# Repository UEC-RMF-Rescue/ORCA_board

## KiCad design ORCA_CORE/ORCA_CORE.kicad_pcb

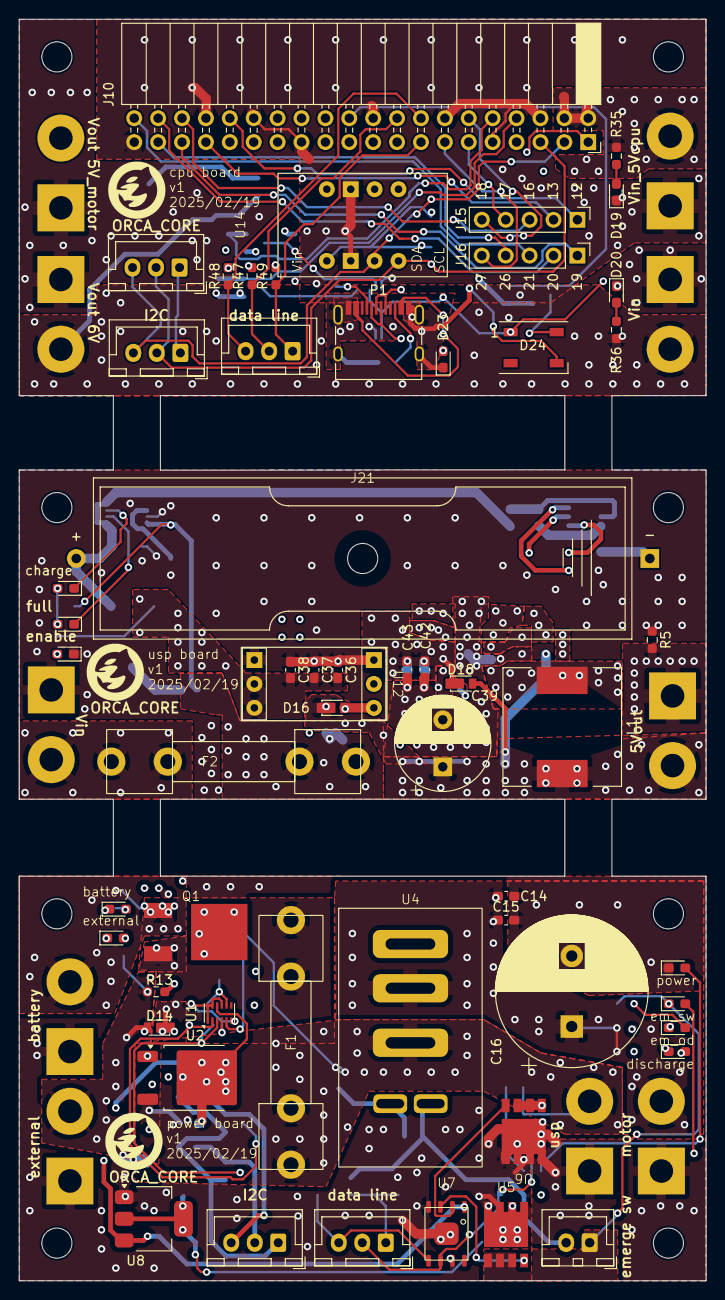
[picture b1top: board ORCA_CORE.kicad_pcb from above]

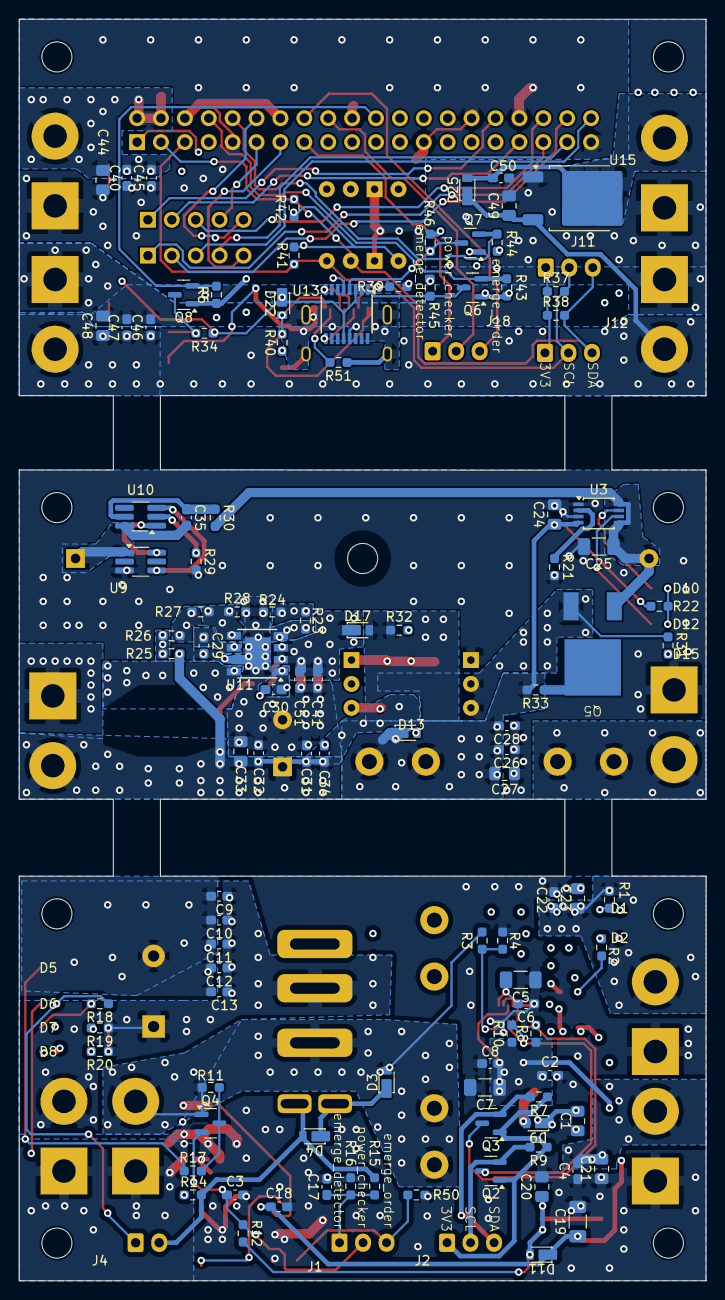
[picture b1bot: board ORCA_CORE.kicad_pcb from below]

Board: 4 copper layers, 73.0 x 134.1 mm, 184 parts (107 on the bottom side), 93 nets.

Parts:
C1, C49: 1u/50V; C_0805_2012Metric_Pad1.18x1.45mm_HandSolder
C2, C50: 0.1u25V; C_0603_1608Metric_Pad1.08x0.95mm_HandSolder
C3, C6, C8, C17, C30, C34, C35, C45: 0.1u; C_0603_1608Metric_Pad1.08x0.95mm_HandSolder
C4, C9, C10, C11, C12, C13, C14, C15, C18, C22, C26, C28, C31, C32, C36, C37, C38, C40, C41, C42, C43, C46, C47, C51: 4.7u; C_0603_1608Metric_Pad1.08x0.95mm_HandSolder
C5, C7, C25: 10u; C_1206_3216Metric_Pad1.33x1.80mm_HandSolder
C16: 4700u; CP_Radial_D16.0mm_P7.50mm
C19: 10u/50V; C_1206_3216Metric_Pad1.33x1.80mm_HandSolder
C20: 22u25V; C_0805_2012Metric_Pad1.18x1.45mm_HandSolder
C21, C23, C24, C27, C33, C44, C48: 1u; C_0805_2012Metric_Pad1.18x1.45mm_HandSolder
C29: 0.01u; C_0603_1608Metric_Pad1.08x0.95mm_HandSolder
C39: 1000u; CP_Radial_D10.0mm_P5.00mm
D1: LED_batt; LED_0603_1608Metric_Pad1.05x0.95mm_HandSolder
D2: LED_ex; LED_0603_1608Metric_Pad1.05x0.95mm_HandSolder
D3, D4, D9, D11, D13, D14, D16, D17, D18, D22, D25: CUHS20560; Diode_US2H
D5: LED_power; LED_0603_1608Metric_Pad1.05x0.95mm_HandSolder
D6: LED_emerge_switch; LED_0603_1608Metric_Pad1.05x0.95mm_HandSolder
D7: LED_emerge_order; LED_0603_1608Metric_Pad1.05x0.95mm_HandSolder
D8: LED_discharge; LED_0603_1608Metric_Pad1.05x0.95mm_HandSolder
D10: LED_charge; LED_0603_1608Metric_Pad1.05x0.95mm_HandSolder
D12: LED_full; LED_0603_1608Metric_Pad1.05x0.95mm_HandSolder
D15: LED_batt_enabled; LED_0603_1608Metric_Pad1.05x0.95mm_HandSolder
D19: LED_cpu; LED_0603_1608Metric_Pad1.05x0.95mm_HandSolder
D20: LED_motor; LED_0603_1608Metric_Pad1.05x0.95mm_HandSolder
D23: LED_usb; LED_0603_1608Metric_Pad1.05x0.95mm_HandSolder
D24: WS2812B; LED_WS2812B_PLCC4_5.0x5.0mm_P3.2mm
F1, F2: Fuse; fuse
H1, H2, H3, H4: Hole_power; MountingHole_3.2mm_M3
H5, H6: Hole_usp; MountingHole_3.2mm_M3
H9: Hole_cpu; MountingHole_3.2mm_M3
H10: Hole_cup; MountingHole_3.2mm_M3
J1, J18: data_line_power; JST_XH_B3B-XH-A_1x03_P2.50mm_Vertical
J2: I2C_power; JST_XH_B3B-XH-A_1x03_P2.50mm_Vertical
J3: Vout_motor; power_pad
J4: emergence; JST_XH_B2B-XH-A_1x02_P2.50mm_Vertical
J5: Vin_batt; power_pad
J6: Vin_ex; power_pad
J7: Vout_power2usp; power_pad
J8: Vin_power2usp; power_pad
J9: +5Vout_cpu; power_pad
J10: Raspberry_Pi_2_3; raspberrypi_Zero_W_Vertical
J11, J12: I2C; JST_XH_B3B-XH-A_1x03_P2.50mm_Vertical
J13: 6Vout; power_pad
J15, J16: Conn_01x05_Pin; PinHeader_1x05_P2.54mm_Vertical
J17: Vin_motor; power_pad
J19: +5Vin_cpu; power_pad
J20: 5Vout; power_pad
J21: Conn_01x02; BatteryHolder_1xAA_code
L1: 10u; L_12x12mm_H8mm_withmodel
ORCA_CORE: LOGO; ORCA_logo
ORCA_CORE#2, ORCA_CORE#3: LOGO; ORCA_logo
P1: USB_C_Receptacle_USB2.0; USB_C_Receptacle_XKB_U262-16XN-4BVC11
Q1, Q5: TJ60S04M3L; 2-7M1A
Q2, Q3, Q6, Q7, Q8: BSS138; SOT-23
Q4: IRLML6402; SOT-23
R1, R2, R14, R17, R18, R20, R22, R31, R35, R36, R40: 1k; R_0603_1608Metric_Pad0.98x0.95mm_HandSolder
R3, R4, R13, R15, R16, R26: 4.7k; R_0603_1608Metric_Pad0.98x0.95mm_HandSolder
R5: 0; R_0603_1608Metric_Pad0.98x0.95mm_HandSolder
R6, R7, R8, R9, R10, R11, R12, R34, R37, R38, R41, R42, R43, R44, R45, R46, R47, R48, R49, R50: 2.2k; R_0603_1608Metric_Pad0.98x0.95mm_HandSolder
R19: 360; R_0603_1608Metric_Pad0.98x0.95mm_HandSolder
R21: 1.2k; R_0603_1608Metric_Pad0.98x0.95mm_HandSolder
R23, R24: 100k; R_0603_1608Metric_Pad0.98x0.95mm_HandSolder
R25: 47k; R_0603_1608Metric_Pad0.98x0.95mm_HandSolder
R27: 510; R_0603_1608Metric_Pad0.98x0.95mm_HandSolder
R28, R32, R33: 10k; R_0603_1608Metric_Pad0.98x0.95mm_HandSolder
R29: 2k; R_0603_1608Metric_Pad0.98x0.95mm_HandSolder
R30: 100; R_0603_1608Metric_Pad0.98x0.95mm_HandSolder
R39, R51: 5.1k; R_0603_1608Metric_Pad0.98x0.95mm_HandSolder
U1: LTC2301IMS; TDFN-12_2x3mm_P0.5mm
U2, U15: NJM78055DL1; TO-252-2
U3: CN3058E; TSSOP-8_3x3mm_P0.65mm
U4: RH1B-UDC6V; RH1-U
U5, U6: TPH11006NL; 2-5Q1S
U7: NJW4860; TSOP8-M1
U8: AZ1117-3.3; SOT-223-3_TabPin2
U9: FS8205; TSOT-23-6_HandSoldering
U10: HY2112; TSOT-23-6_HandSoldering
U11: AP64502; Diodes_SO-8EP
U12: TPS61230A__board; TPS61230A
U13: FT230XS; SSOP-16_3.9x4.9mm_P0.635mm
U14: BNO055

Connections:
+3V3_cpu: J10.1 (3V3), J10.17 (3V3), J11.1, J12.1, Q6.1 (G), Q7.1 (G), Q8.1 (G), R6.1, R37.1, R38.1, R41.1, R42.1, R43.1, R44.1, U14.1 (VDD)
+3V3_power: C20.1, D11.2 (A), R12.2, U8.2 (Vout)
+5V_cpu: C40.1, C44.1, C45.1, D22.1 (K), D24.1 (VDD), J10.2 (5V), J10.4 (5V), J19.2, R34.1, R35.1, R45.1, R46.1, U13.3 (VCCIO), U13.12 (VCC)
+5V_cpu2servo: C50.1, D25.2 (A), J20.2, U15.2 (Vout)
+5V_power: C2.1, C7.1, C8.1, C18.1, C19.1, D9.2 (A), D11.1 (K), R8.1, R10.1, U1.10 (VDD), U2.2 (Vout), U7.1 (Vdd), U8.3 (Vin)
+6V_cpu: C46.1, C47.1, C48.1, C49.1, D25.1 (K), J13.2, J17.2, R36.1, U15.3 (Vin)
+6V_power: C1.1, D3.2 (A), D9.1 (K), F1.2, J7.2, Q4.1 (G), R3.1, R11.2, U2.3 (Vin), U4.9
+BATT_power: C22.2, C23.2, J5.2, Q1.1 (D), R1.2
+VDD_power: C4.2, C21.2, D14.2 (A), J6.2, R2.1, R13.2
+VDD_usp: C24.1, C26.2, C27.2, C28.2, D13.1 (K), D17.2 (A), F2.1, R22.1, R32.1, R33.2, U3.4 (VIN)
/cpu/GPIO12: J10.32 (PWM0/GPIO12), J15.1
/cpu/GPIO13: J10.33 (PWM1/GPIO13), J15.2
/cpu/GPIO16: J10.36 (GPIO16), J15.3
/cpu/GPIO17: J10.11 (GPIO17), J15.4
/cpu/GPIO18: J10.12 (GPIO18/PWM0), J15.5
/cpu/GPIO19: J10.35 (GPIO19/MISO1), J16.1
/cpu/GPIO20: J10.38 (GPIO20/MOSI1), J16.2
/cpu/GPIO21: J10.40 (GPIO21/SCLK1), J16.3
/cpu/GPIO26: J10.37 (GPIO26), J16.4
/cpu/GPIO27: J10.13 (GPIO27), J16.5
/cpu/emerg_detector: J10.15 (GPIO22), J18.1, R49.1
/cpu/emerge_order: J10.16 (GPIO23), J18.3, R48.1
/cpu/power_checker: J10.18 (GPIO24), J18.2, R47.1
/power/SCL_3V3: J2.2, Q2.2 (S), R9.2
/power/SDA_3V3: J2.3, Q3.2 (S), R7.2
/power/Vout_motor: C9.1, C10.1, C11.1, C12.1, C13.1, C14.1, C15.1, C16.1, J3.2, R19.1, R20.1, U4.5
/power/emerg_detector: C17.1, J1.1, R15.2, R16.1
/power/emerge_order: J1.3, R50.2, U7.5 (INB)
/power/power_checker: C3.1, J1.2, Q4.2 (S), R12.1, U7.6 (INA)
/usp/Vin: F2.2, J8.2
GND: C1.2, C2.2, C3.2, C4.1, C5.1, C6.1, C7.2, C8.2, C9.2, C10.2, C11.2, C12.2, C13.2, C14.2, C15.2, C16.2, C17.2, C18.2, C19.2, C20.2, C21.1, C22.1, C23.1, C24.2, C25.2, C26.1, C27.1, C28.1, C29.2, C31.1, C32.1, C33.1, C34.1, C36.1, C37.1, C38.1, C39.2, C41.1, C42.1, C43.1, C46.2, C47.2, C48.2, C49.2, C50.2, C51.1, D1.1 (K), D2.1 (K), D5.1 (K), D7.1 (K), D13.2 (A), D15.1 (K), D20.1 (K), J3.1, J5.1, J6.1, J7.1, J8.1, J13.1, J17.1, J20.1, R4.2, R5.1, R16.2, R21.2, R24.2, R28.2, R29.2, R32.2, R50.1, U1.1 (GND), U1.4 (GND), U1.6 (IN-), U1.9 (GDN), U1.11 (AD1), U1.12 (AD0), U2.1 (GND), U3.1 (TEMP), U3.3 (GND), U5.5, U5.6, U5.7, U5.8, U6.5, U6.6, U6.7, U6.8, U7.4 (GND), U7.7 (GND), U8.1 (GND), U9.3, U11.7 (GND), U11.9 (PAD), U12.3 (GND), U15.1 (GND)
GND1: J9.1, R5.2
GND2: C40.2, C44.2, C45.2, D19.1 (K), D23.1 (K), D24.3 (VSS), J10.6 (GND), J10.9 (GND), J10.14 (GND), J10.20 (GND), J10.25 (GND), J10.30 (GND), J10.34 (GND), J10.39 (GND), J19.1, P1.A1 (GND), P1.A12 (GND), P1.B1 (GND), P1.B12 (GND), P1.S1 (SHIELD), R39.1, R47.2, R48.2, R49.2, R51.1, U13.5 (GND), U13.13 (GND), U14.2 (GND), U14.7 (GND)
unnamed: D1.2 (A), R1.1
unnamed: D2.2 (A), R2.2
unnamed: D3.1 (K), D4.1 (K), U4.14
unnamed: D4.2 (A), J4.2, R14.1, R15.1, U4.13
unnamed: D5.2 (A), R17.1
unnamed: D6.2 (A), R14.2
unnamed: D6.1 (K), J4.1, R18.1, U5.1, U5.2, U5.3
unnamed: D7.2 (A), R18.2
unnamed: D8.2 (A), R20.2
unnamed: D8.1 (K), R19.2, U6.1, U6.2, U6.3
unnamed: D10.2 (A), D12.2 (A), R22.2
unnamed: D10.1 (K), U3.7 (CHRG)
unnamed: D12.1 (K), U3.6 (DONE)
unnamed: D14.1 (K), F1.1, Q1.3 (S)
unnamed: D15.2 (A), R31.2
unnamed: D19.2 (A), R35.2
unnamed: D20.2 (A), R36.2
unnamed: D22.2 (A), P1.A4 (VBUS), P1.A9 (VBUS), P1.B4 (VBUS), P1.B9 (VBUS), R40.1
unnamed: D23.2 (A), R40.2
unnamed: P1.A5 (CC1), R39.2
unnamed: P1.B5 (CC2), R51.2
unnamed: Q1.2 (G), R13.1
unnamed: Q4.3 (D), R11.1, R17.2
unnamed: Q5.2 (G), R33.1
unnamed: R23.2, R24.1
unnamed: R25.1, R26.1
unnamed: R26.2, R27.1
unnamed: R3.2, R4.1, U1.5 (IN+)
unnamed: C5.2, C6.2, U1.8 (REFCOMP)
unnamed: R21.1, U3.2 (ISET)
unnamed: U6.4, U7.2 (OUTA)
unnamed: U5.4, U7.3 (OUTB)
unnamed: R29.1, U10.2 (CS)
unnamed: U9.4, U10.3 (OC)
unnamed: U9.6, U10.1 (OD)
unnamed: C35.1, R30.1, U10.5 (VDD)
unnamed: C30.2, U11.1 (BST)
unnamed: R27.2, R28.1, U11.5 (FB)
unnamed: R23.1, U11.4 (RT/CLK)
unnamed: C29.1, U11.6 (SS)
unnamed: C30.1, L1.1, U11.8 (SW)
unnamed: P1.A7 (D-), P1.B7 (D-), U13.9 (USBDM)
unnamed: P1.A6 (D+), P1.B6 (D+), U13.8 (USBDP)
RXD_3V3: J10.10 (GPIO15/RXD), Q7.2 (S), R44.2
RXD_5V: Q7.3 (D), R46.2, U13.4 (RXD)
SCL: J10.5 (SCL/GPIO3), J11.2, J12.2, R37.2, R41.2, U14.4 (SCL)
SCL_5V: Q2.3 (D), R10.2, U1.3 (SCL)
SDA: J10.3 (SDA/GPIO2), J11.3, J12.3, R38.2, R42.2, U14.3 (SDA)
SDA_5V: Q3.3 (D), R8.2, U1.2 (SDA)
TXD_3V3: J10.8 (GPIO14/TXD), Q6.2 (S), R43.2
TXD_5V: Q6.3 (D), R45.2, U13.1 (TXD)
VBUS_power: J2.1, Q2.1 (G), Q3.1 (G), R7.1, R9.1
batt+: C25.1, J21.2, Q5.1 (D), R30.2, U3.5 (BAT), U3.8 (FB)
batt-: C35.2, J21.1, U9.1, U10.6 (VSS)
full_color_led_3V3: J10.22 (GPIO25), Q8.2 (S), R6.2
full_color_led_5V: D24.4 (DIN), Q8.3 (D), R34.2
reg_down: C41.2, C42.2, C43.2, C51.2, D17.1 (K), D18.1 (K), U11.2 (Vin), U11.3 (EN)
reg_down_out: C31.2, C32.2, C33.2, C34.2, C39.1, D16.1 (K), D18.2 (A), J9.2, L1.2, R25.2
reg_up: C36.2, C37.2, C38.2, Q5.3 (S), R31.1, U12.1 (VIN), U12.2 (EN)
reg_up_out: D16.2 (A), U12.4 (VOUT)

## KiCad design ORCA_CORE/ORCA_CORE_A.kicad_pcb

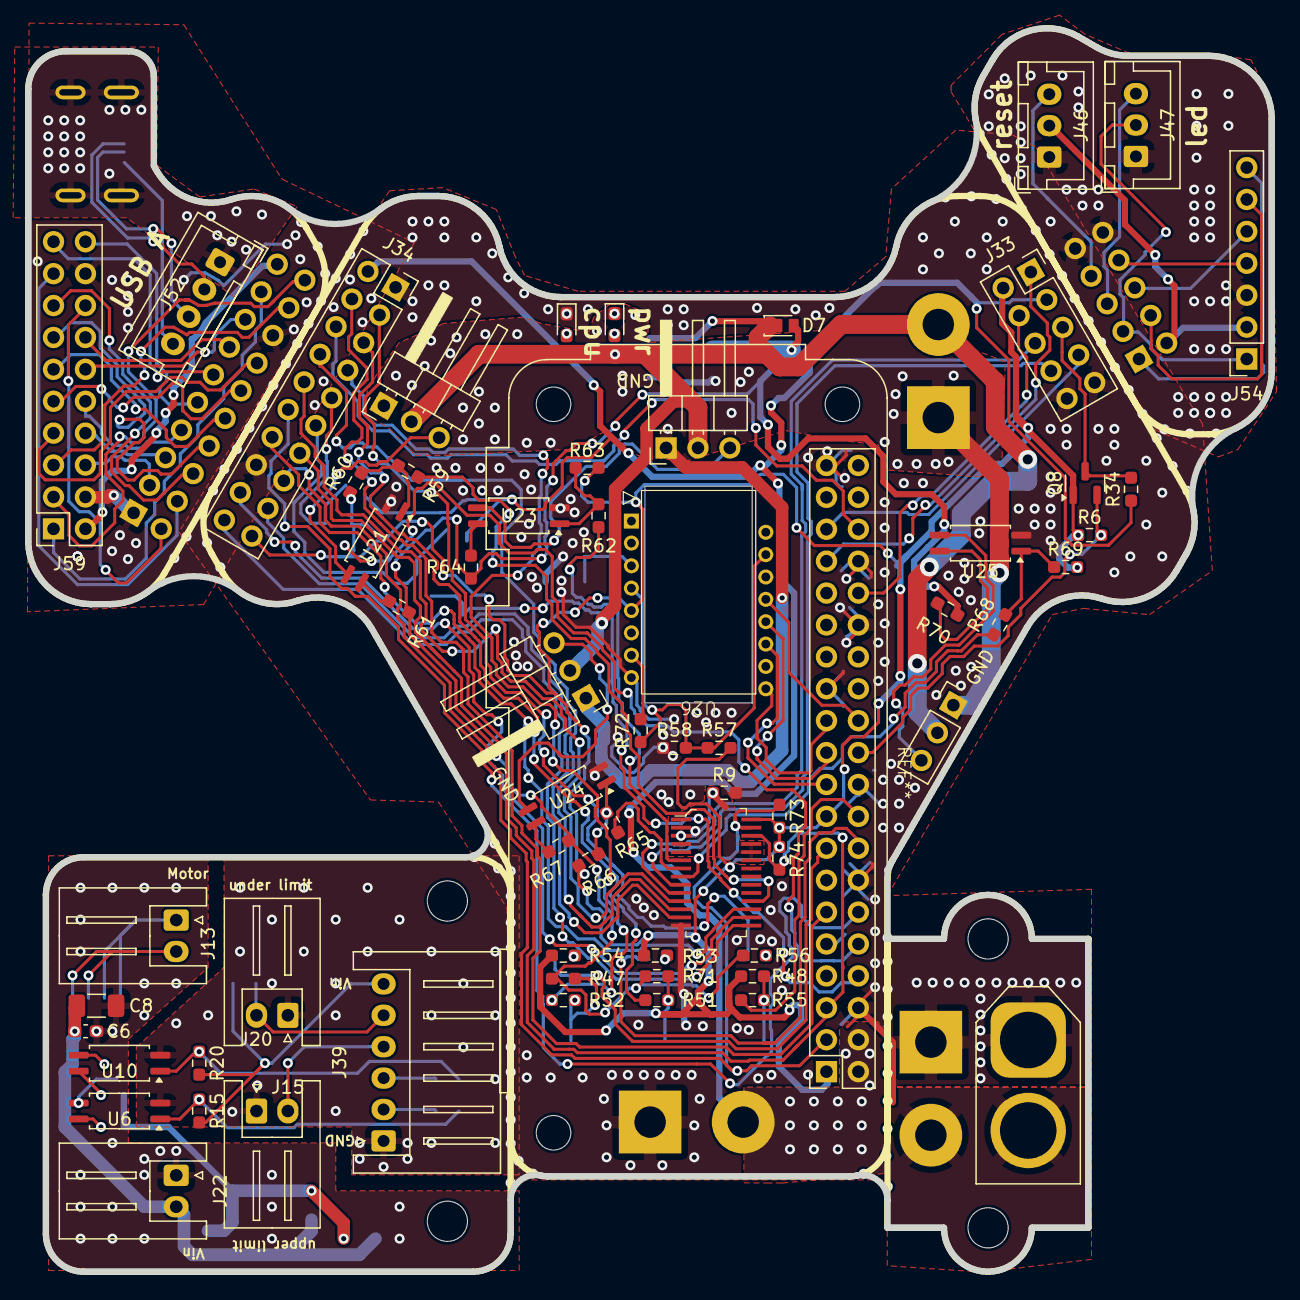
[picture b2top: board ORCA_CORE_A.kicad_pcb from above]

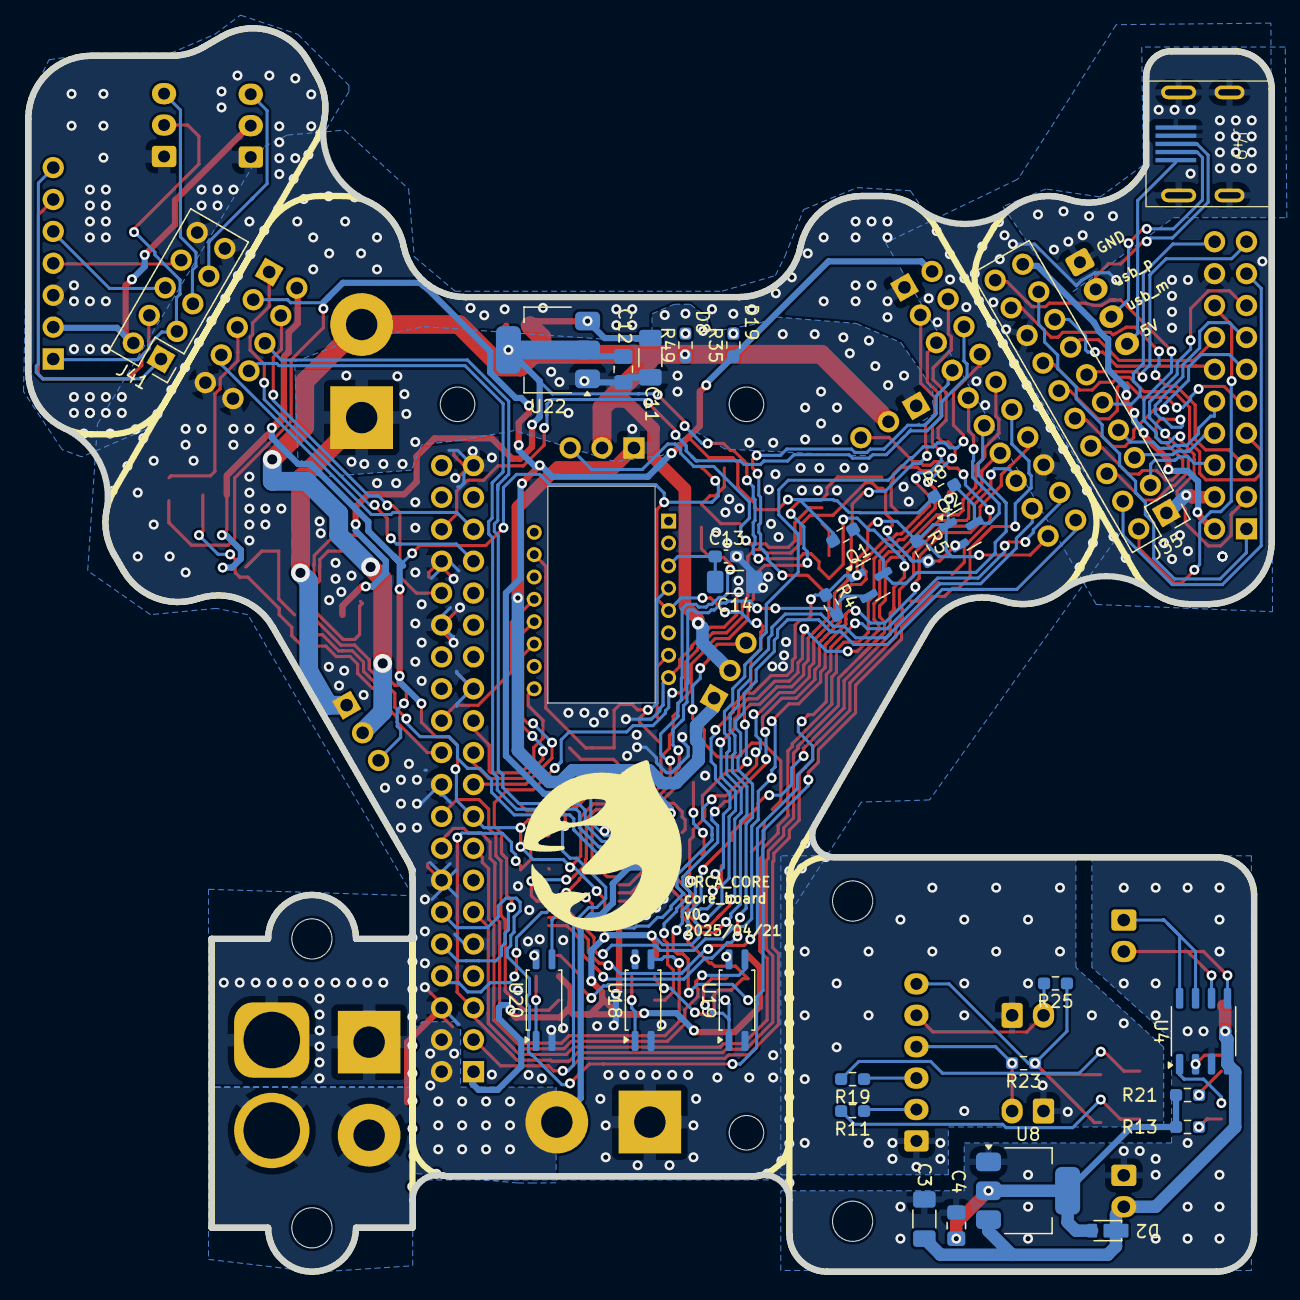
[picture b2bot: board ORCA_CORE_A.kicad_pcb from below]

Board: 2 copper layers, 99.0 x 99.0 mm, 100 parts (30 on the bottom side), 108 nets.

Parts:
C3, C11: 10u/50V; C_1206_3216Metric_Pad1.33x1.80mm_HandSolder
C4, C12: 22u25V; C_0805_2012Metric_Pad1.18x1.45mm_HandSolder
C6, C13: 0.1u; C_0603_1608Metric_Pad1.08x0.95mm_HandSolder
C8: 220u; C_1206_3216Metric_Pad1.33x1.80mm_HandSolder
C14: 10u; C_1206_3216Metric_Pad1.33x1.80mm_HandSolder
D2, D7: CUHS20560; Diode_US2H
D8: pwr_motor; LED_0603_1608Metric_Pad1.05x0.95mm_HandSolder
D19: pwr_cpu; LED_0603_1608Metric_Pad1.05x0.95mm_HandSolder
H7, H8: Hole_Vext; MountingHole_3.2mm_M3
H15, H16: Hole_md; MountingHole_3.2mm_M3
J1: Vext_in; AMASS_XT60_Vertifcal_withmodel_female
J6: Vext_out; power_pad
J8: wheel_front; PinHeader_1x03_P2.54mm_Horizontal
J9: wheel_right; PinHeader_1x03_P2.54mm_Horizontal
J10: Raspberry_Pi_2_3; raspberrypi_Zerp_W_horisontal
J11: wheel_left; PinHeader_1x03_P2.54mm_Vertical
J13: md_out; JST_XH_S2B-XH-A_1x02_P2.50mm_Horizontal
J15: limit_sw_upper; JST_XH_S2B-XH-A_1x02_P2.50mm_Horizontal
J18: +6V_motor; power_pad
J19: +5Vin_cpu; power_pad
J20: limit_sw_under; JST_XH_S2B-XH-A_1x02_P2.50mm_Horizontal
J22: Vin_motor; JST_XH_S2B-XH-A_1x02_P2.50mm_Horizontal
J33: cpu_female_left; PinSocket_2x05_P2.54mm_Vertical
J34: cpu_female_right; PinSocket_2x10_P2.54mm_Vertical
J35: hat_male_right; PinHeader_2x10_P2.54mm_Vertical
J39: md_arm; JST_XH_S6B-XH-A_1x06_P2.50mm_Horizontal
J41: cpu_male_left; PinHeader_2x05_P2.54mm_Vertical
J44: servo_camera; PinHeader_1x03_P2.54mm_Horizontal
J46: reset; JST_XH_B3B-XH-A_1x03_P2.50mm_Vertical
J47: led; JST_XH_B3B-XH-A_1x03_P2.50mm_Vertical
J49: USB_B_Micro; ZX60-B-5S(31)
J52: usb_A; JST_XH_B4B-XH-A_1x04_P2.50mm_Vertical
J54: base_left; PinSocket_1x07_P2.54mm_Vertical
J59: base_right; PinSocket_2x10_P2.54mm_Vertical
Q1, Q2, Q8: BSS138; SOT-23
R4, R5, R6, R7, R8, R13, R15, R20, R21, R23, R25, R34, R47, R48, R53, R54, R56, R60, R61, R63, R64, R66, R67, R69, R70, R71, R73, R74: 2.2k; R_0603_1608Metric_Pad0.98x0.95mm_HandSolder
R9, R72: 10k; R_0603_1608Metric_Pad0.98x0.95mm_HandSolder
R11, R19, R51, R52, R55, R59, R62, R65, R68: 100; R_0603_1608Metric_Pad0.98x0.95mm_HandSolder
R35, R49: 1k; R_0603_1608Metric_Pad0.98x0.95mm_HandSolder
R57: 1.2k; R_0603_1608Metric_Pad0.98x0.95mm_HandSolder
R58: 2k; R_0603_1608Metric_Pad0.98x0.95mm_HandSolder
U2: PCA9685PW_Q900_118; TSSOP-28_W4.40mm
U4: AM2837; SOP-8_3.9x4.9mm_P1.27mm
U6, U10, U18, U19, U20, U21, U23, U24, U25: TLP293; SOIC-4_4.55x2.6mm_P1.27mm
U8, U22: AZ1117-3.3; SOT-223-3_TabPin2
U26: PMW3360

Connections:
+3V3: C4.1, D2.2 (A), J10.1 (3V3), J10.17 (3V3), J33.2, J34.19, Q1.1 (G), Q2.1 (G), Q8.1 (G), R4.1, R5.1, R6.1, R13.2, R21.2, R48.2, R53.2, R54.2, R57.2, R60.2, R63.2, R66.2, R69.2, R73.2, R74.2, U2.28 (VDD), U8.2 (Vout), U26.5 (VDDIO)
+3V3_motor: C12.1, D7.2 (A), R47.2, R56.2, R61.2, R64.2, R67.2, R70.2, R71.2, U22.2 (Vout)
+5V: J10.2 (5V), J10.4 (5V), J19.2, J33.3, J34.2, R7.1, R8.1, R34.1, R35.1
+6V: C3.1, C6.1, C8.1, C11.1, D2.1 (K), D7.1 (K), J8.2, J9.2, J11.2, J18.2, J22.2, J44.2, R49.1, U4.4 (VCC), U8.3 (Vin), U22.3 (Vin)
/cpu/GPIO12: J10.32 (PWM0/GPIO12), J33.4
/cpu/GPIO13: J10.33 (PWM1/GPIO13), J33.1
/cpu/GPIO16: J10.36 (GPIO16), J34.6
/cpu/GPIO17: J10.11 (GPIO17), J34.4
/cpu/GPIO18: J10.12 (GPIO18/PWM0), J34.12
/cpu/LED0: R62.1, U2.6 (LED0)
/cpu/LED1: R65.1, U2.7 (LED1)
/cpu/LED2: R68.1, U2.8 (LED2)
/cpu/LED3: J33.8, U2.9 (LED3)
/cpu/LED4: J33.6, U2.10 (LED4)
/cpu/LED5: J34.10, U2.11 (LED5)
/cpu/LED6: J34.8, U2.12 (LED6)
/cpu/LED7: J34.17, U2.13 (LED7)
/cpu/LED8: J34.20, U2.15 (LED8)
/cpu/LED9: J34.18, U2.16 (LED9)
/cpu/LED10: J34.14, U2.17 (LED10)
/cpu/LED11: R59.1, U2.18 (LED11)
/cpu/RXD_5V: J34.9, Q2.3 (D), R8.2
/cpu/TXD_5V: J34.11, Q1.3 (D), R7.2
/cpu/emerge_detector: J34.7, R52.1
/cpu/emerge_order: J34.3, U20.3
/cpu/led: J33.5, Q8.3 (D), R34.2
/cpu/power_checker: J34.5, R51.1
/cpu/rest: J10.35 (GPIO19/MISO1), J33.7
/cpu_hat/+5V_usb: J49.1 (VBUS), J52.4
/cpu_hat/GND_usb: J49.4 (ID), J49.5 (GND), J49.SH (Shield), J52.1
/cpu_hat/IN_A_arm: J35.10, J59.11
/cpu_hat/IN_A_fork: J41.8, J54.4
/cpu_hat/IN_B_arm: J35.8, J59.13
/cpu_hat/IN_B_fork: J41.6, J54.5
/cpu_hat/RX: J35.9, J59.20
/cpu_hat/SCL: J35.13, J59.14
/cpu_hat/SDA: J35.15, J59.12
/cpu_hat/TX: J35.11, J59.19
/cpu_hat/emerge_detector: J35.7, J59.10
/cpu_hat/emerge_order: J35.3, J59.6
/cpu_hat/enable_arm: J35.12, J59.9
/cpu_hat/led: J41.5, J47.3
/cpu_hat/limit_sw_under_arm: J35.4, J59.17
/cpu_hat/limit_sw_under_fork: J41.1, J54.7
/cpu_hat/limit_sw_upper_arm: J35.6, J59.15
/cpu_hat/limit_sw_upper_fork: J41.4, J54.6
/cpu_hat/power_checker: J35.5, J59.8
/cpu_hat/reset: J41.7, J46.3
/cpu_hat/servo_0: J35.17, J59.1
/cpu_hat/servo_1: J35.20, J59.3
/cpu_hat/servo_2: J35.18, J59.5
/cpu_hat/servo_3: J35.14, J59.7
/cpu_hat/usb_m: J49.2 (D-), J52.3
/cpu_hat/usb_p: J49.3 (D+), J52.2
/md_arm/IN_A: J39.2, R11.1
/md_arm/IN_B: J39.3, R19.1
/md_arm/limit_sw_under: J20.2, J39.5, R25.2
/md_arm/limit_sw_upper: J15.2, J39.4, R23.2
CS0: J10.24 (~CE0/GPIO8), U26.13 (NCS)
GND: C3.2, C4.2, C6.2, C8.2, C11.2, C12.2, D8.1 (K), J8.1, J9.1, J11.1, J18.1, J22.1, J44.1, U4.3 (GND), U8.1 (GND), U22.1 (GND)
GND1: C13.1, C14.1, D19.1 (K), J1.1, J6.1, J10.6 (GND), J10.9 (GND), J10.14 (GND), J10.20 (GND), J10.25 (GND), J10.30 (GND), J10.34 (GND), J10.39 (GND), J15.1, J19.1, J20.1, J33.9, J33.10, J34.1, J34.16, J35.1, J35.16, J39.1, J41.9, J41.10, J46.1, J47.1, J54.3, J59.4, J59.18, R9.2, R58.1, U2.14 (VSS), U6.2, U10.2, U18.2, U19.2, U20.2, U21.2, U23.2, U24.2, U25.2, U26.8 (GND)
MISO: J10.21 (MISO0/GPIO9), U26.12 (MISO)
MOSI: J10.19 (MOSI0/GPIO10), U26.11 (MOSI)
unnamed: D8.2 (A), R49.2
unnamed: D19.2 (A), R35.2
unnamed: J1.2, J6.2
unnamed: J8.3, U23.3
unnamed: J9.3, U24.3
unnamed: J11.3, U25.3
unnamed: J13.1, U4.7 (OUT_A2), U4.8 (OUT_A1)
unnamed: J13.2, U4.5 (OUT_B2), U4.6 (OUT_B1)
unnamed: J44.3, U21.3
unnamed: R11.2, R15.1, U6.1
unnamed: R13.1, U6.4
unnamed: R19.2, R20.1, U10.1
unnamed: R21.1, U10.4
unnamed: R47.1, R52.2, U19.1
unnamed: R48.1, R55.2, U20.1
unnamed: R51.2, R71.1, U18.1
unnamed: R53.1, U18.4
unnamed: R54.1, U19.4
unnamed: R56.1, U20.4
unnamed: R59.2, R60.1, U21.1
unnamed: R61.1, U21.4
unnamed: R62.2, R63.1, U23.1
unnamed: R64.1, U23.4
unnamed: R65.2, R66.1, U24.1
unnamed: R67.1, U24.4
unnamed: R68.2, R69.1, U25.1
unnamed: R70.1, U25.4
unnamed: R9.1, U2.1 (A0), U2.2 (A1), U2.3 (A2), U2.4 (A3), U2.5 (A4), U2.23 (~OE), U2.24 (A5), U2.25 (EXTCLK)
unnamed: U4.1 (IN_A), U6.3
unnamed: U4.2 (IN_B), U10.3
unnamed: R57.1, R58.2, R72.1, U26.4 (VDD), U26.15 (LED_P)
unnamed: R72.2, U26.7 (NRESET)
unnamed: C13.2, C14.2, U26.3 (VDDPIX)
RXD_3V3: J10.10 (GPIO15/RXD), Q2.2 (S), R5.2
SCL: J10.5 (SCL/GPIO3), J34.13, R74.1, U2.26 (SCL)
SCLK: J10.23 (SCLK0/GPIO11), U26.9 (SCLK)
SDA: J10.3 (SDA/GPIO2), J34.15, R73.1, U2.27 (SDA)
TXD_3V3: J10.8 (GPIO14/TXD), Q1.2 (S), R4.2
Vin_3V3_cpu_hat: J35.19, J41.2, J46.2, J54.2, J59.2
Vin_cpu_hat: J35.2, J41.3, J47.2, J54.1, J59.16
Vin_md: J39.6, R15.2, R20.2, R23.1, R25.1
emerge_detector_out: J10.15 (GPIO22), U19.3
emerge_order_in: J10.18 (GPIO24), R55.1
full_color_led_3V3: J10.22 (GPIO25), Q8.2 (S), R6.2
power_checker_out: J10.16 (GPIO23), U18.3

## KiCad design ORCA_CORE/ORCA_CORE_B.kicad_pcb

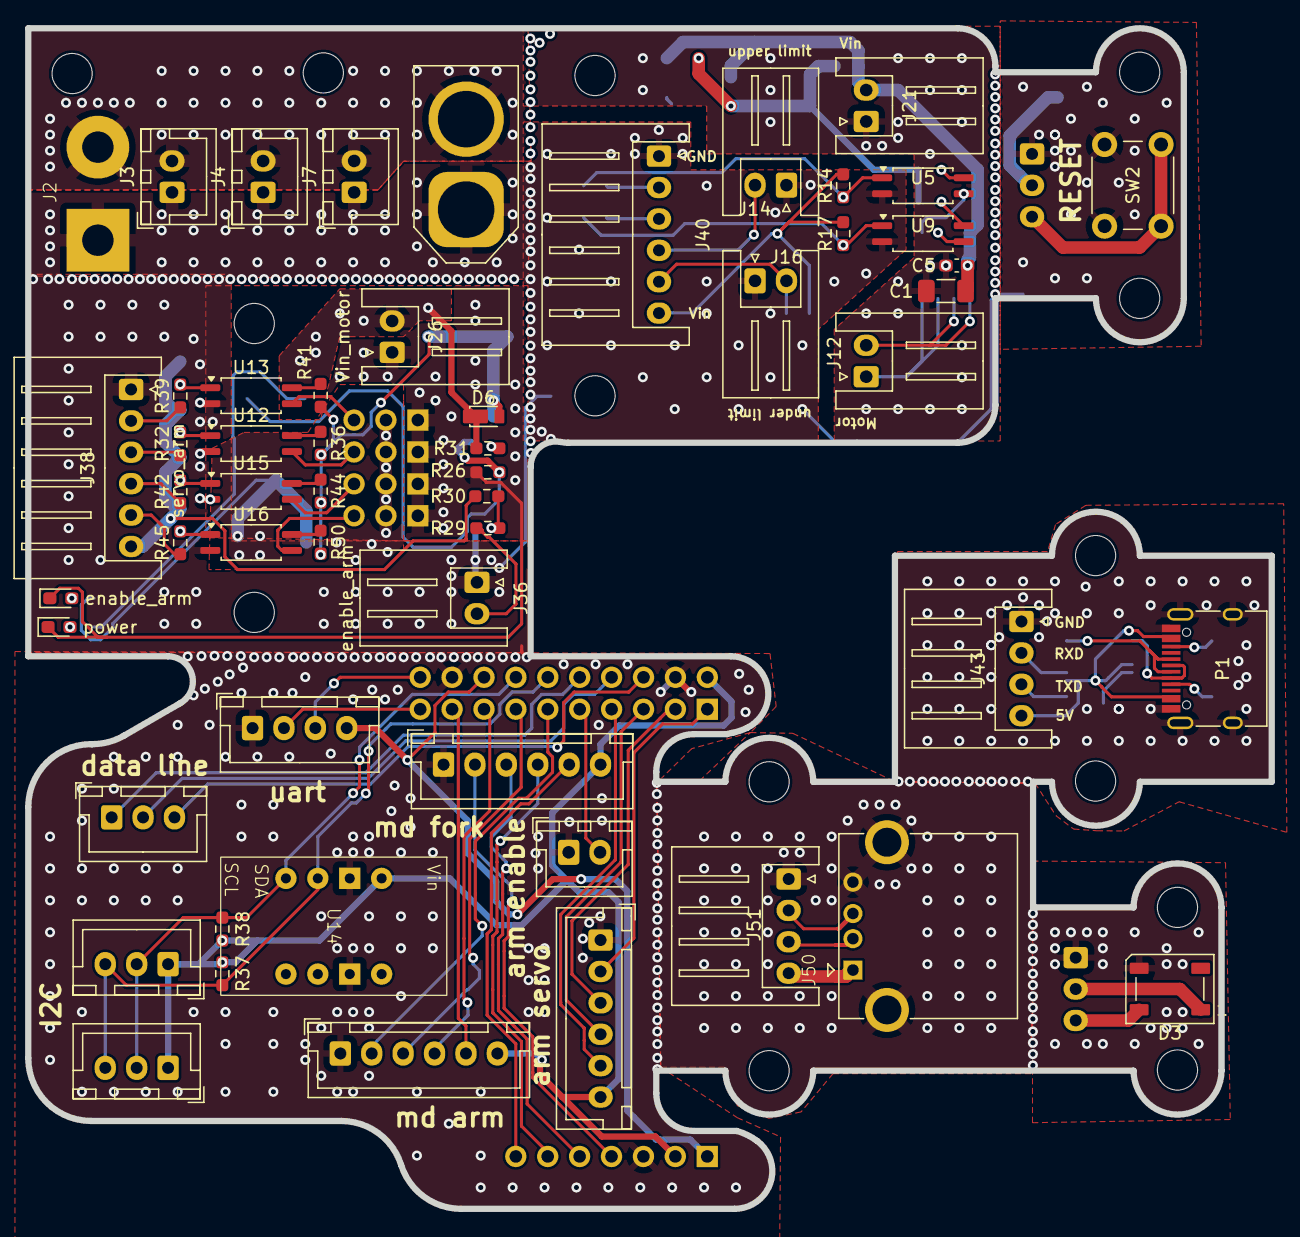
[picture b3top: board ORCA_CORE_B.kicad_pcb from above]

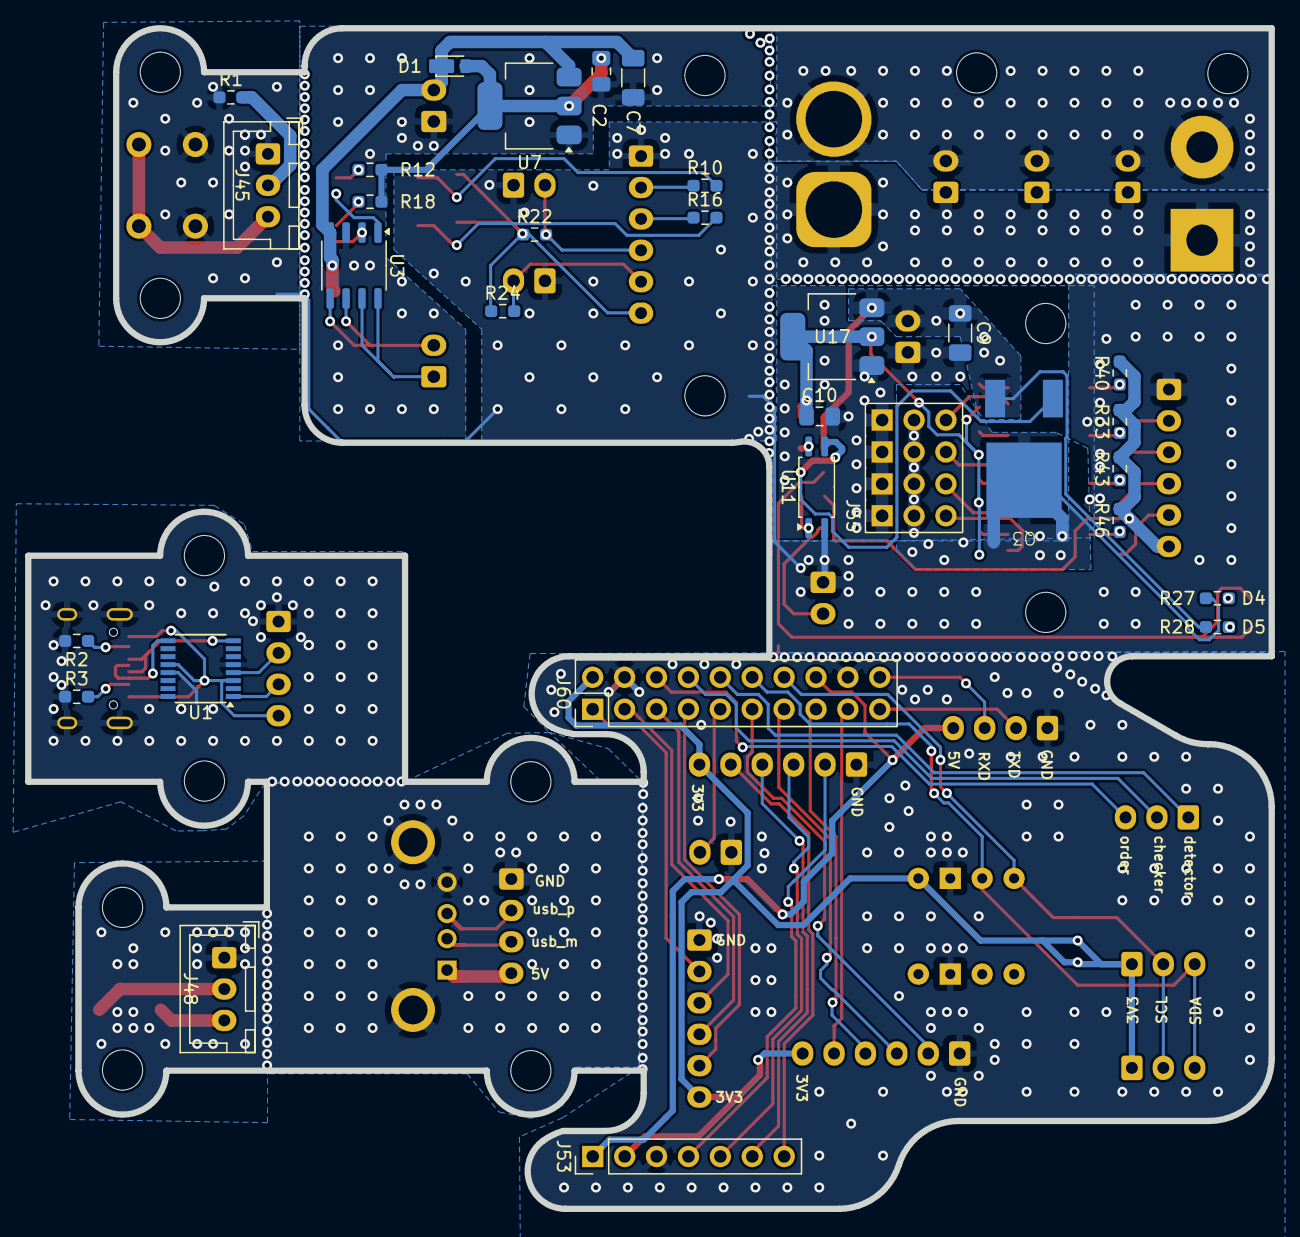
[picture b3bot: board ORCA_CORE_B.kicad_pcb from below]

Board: 2 copper layers, 99.0 x 94.0 mm, 100 parts (31 on the bottom side), 79 nets.

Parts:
C1, C9: 10u/50V; C_1206_3216Metric_Pad1.33x1.80mm_HandSolder
C2, C10: 22u25V; C_0805_2012Metric_Pad1.18x1.45mm_HandSolder
C5: 0.1u; C_0603_1608Metric_Pad1.08x0.95mm_HandSolder
C7: 220u; C_1206_3216Metric_Pad1.33x1.80mm_HandSolder
D1, D6: CUHS20560; Diode_US2H
D3: WS2812B; LED_WS2812B_PLCC4_5.0x5.0mm_P3.2mm
D4: enable_arm; LED_0603_1608Metric_Pad1.05x0.95mm_HandSolder
D5: power; LED_0603_1608Metric_Pad1.05x0.95mm_HandSolder
H1, H2: Hole_uart; MountingHole_3.2mm_M3
H3, H4: Hole_led; MountingHole_3.2mm_M3
H5, H6: Hole_reset; MountingHole_3.2mm_M3
H11, H12: Hole_Vhub; MountingHole_3.2mm_M3
H13, H14: Hole_md; MountingHole_3.2mm_M3
H23, H24: Hole_usbA; MountingHole_3.2mm_M3
H25, H26: Hole_arm; MountingHole_3.2mm_M3
J2: 6Vout; power_pad
J3, J4, J7: 6Vout; JST_XH_B2B-XH-A_1x02_P2.50mm_Vertical
J5: 6Vin; AMASS_XT60_Vertifcal_withmodel_female
J12: md_out; JST_XH_S2B-XH-A_1x02_P2.50mm_Horizontal
J14: limit_sw_upper; JST_XH_S2B-XH-A_1x02_P2.50mm_Horizontal
J16: limit_sw_under; JST_XH_S2B-XH-A_1x02_P2.50mm_Horizontal
J17: data_line_power; JST_XH_B3B-XH-A_1x03_P2.50mm_Vertical
J21, J26: Vin_motor; JST_XH_S2B-XH-A_1x02_P2.50mm_Horizontal
J23: md_arm; JST_XH_B6B-XH-A_1x06_P2.50mm_Vertical
J24: md_fork; JST_XH_B6B-XH-A_1x06_P2.50mm_Vertical
J25: servo_arm; JST_XH_B6B-XH-A_1x06_P2.50mm_Vertical
J31: I2C_1; JST_XH_B3B-XH-A_1x03_P2.50mm_Vertical
J32: I2C_2; JST_XH_B3B-XH-A_1x03_P2.50mm_Vertical
J36: enable_arm; JST_XH_S2B-XH-A_1x02_P2.50mm_Horizontal
J37: enable_arm; JST_XH_B2B-XH-A_1x02_P2.50mm_Vertical
J38: servo_arm; JST_XH_S6B-XH-A_1x06_P2.50mm_Horizontal
J40: md_fork; JST_XH_S6B-XH-A_1x06_P2.50mm_Horizontal
J42: uart; JST_XH_B4B-XH-A_1x04_P2.50mm_Vertical
J43: uart_device; JST_XH_S4B-XH-A_1x04_P2.50mm_Horizontal
J45: reset; JST_XH_B3B-XH-A_1x03_P2.50mm_Vertical
J48: led; JST_XH_B3B-XH-A_1x03_P2.50mm_Vertical
J50: USB_A; TypeA_connector_KUSBX-AS1N-B
J51: usb_A_device; JST_XH_S4B-XH-A_1x04_P2.50mm_Horizontal
J53: cover_left; PinHeader_1x07_P2.54mm_Vertical
J55: servo connectors; PinHeader_03x04_P2.54mm_Vertical
J60: cover_right; PinHeader_2x10_P2.54mm_Vertical
P1: USB_C_Receptacle_USB2.0; USB_C_Receptacle_XKB_U262-16XN-4BVC11
Q3: TJ60S04M3L; 2-7M1A
R1: 560; R_0603_1608Metric_Pad0.98x0.95mm_HandSolder
R2, R3: 5.1k; R_0603_1608Metric_Pad0.98x0.95mm_HandSolder
R10, R16, R29, R32, R39, R42, R45: 100; R_0603_1608Metric_Pad0.98x0.95mm_HandSolder
R12, R14, R17, R18, R22, R24, R30, R33, R36, R37, R38, R40, R41, R43, R44, R46, R50: 2.2k; R_0603_1608Metric_Pad0.98x0.95mm_HandSolder
R26: 10k; R_0603_1608Metric_Pad0.98x0.95mm_HandSolder
R27, R28: 1k; R_0603_1608Metric_Pad0.98x0.95mm_HandSolder
R31: 47; R_0603_1608Metric_Pad0.98x0.95mm_HandSolder
SW2: REST_sw; SW_PUSH_6mm
U1: FT230XS; SSOP-16_3.9x4.9mm_P0.635mm
U3: AM2837; SOP-8_3.9x4.9mm_P1.27mm
U5, U9, U11, U12, U13, U15, U16: TLP293; SOIC-4_4.55x2.6mm_P1.27mm
U7, U17: AZ1117-3.3; SOT-223-3_TabPin2
U14: BNO055

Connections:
+3V3: C2.1, C10.1, D1.2 (A), D6.2 (A), R12.2, R18.2, R36.2, R41.2, R44.2, R50.2, U7.2 (Vout), U17.2 (Vout)
+6V: C1.1, C5.1, C7.1, D1.1 (K), J21.2, U3.4 (VCC), U7.3 (Vin)
+6V_in: C9.1, D6.1 (K), J26.2, Q3.3 (S), R28.2, R31.2, U17.3 (Vin)
+6V_out: J55.2, J55.5, J55.8, J55.11, Q3.1 (D), R27.1
/arm/enable_arm: J36.2, R29.1
/arm/servo_0: J38.2, R39.1
/arm/servo_1: J38.3, R32.1
/arm/servo_2: J38.4, R42.1
/arm/servo_3: J38.5, R45.1
/cpu_hat/IN_A_arm_out: J23.2, J60.11
/cpu_hat/IN_A_fork_out: J24.2, J53.4
/cpu_hat/IN_B_arm_out: J23.3, J60.13
/cpu_hat/IN_B_fork_out: J24.3, J53.5
/cpu_hat/RX_out: J42.3, J60.20
/cpu_hat/TX_out: J42.2, J60.19
/cpu_hat/enable_arm_out: J37.2, J60.9
/cpu_hat/limit_sw_under_arm_in: J23.5, J60.17
/cpu_hat/limit_sw_under_fork_in: J24.5, J53.7
/cpu_hat/limit_sw_upper_arm_in: J23.4, J60.15
/cpu_hat/limit_sw_upper_fork_in: J24.4, J53.6
/cpu_hat/servo_0_out: J25.2, J60.1
/cpu_hat/servo_1_out: J25.3, J60.3
/cpu_hat/servo_2_out: J25.4, J60.5
/cpu_hat/servo_3_out: J25.5, J60.7
/external_io/3V3_reset: J45.2, R1.2
/external_io/+5V_led: D3.1 (VDD), J48.2
/external_io/+5V_uart: J43.4, P1.A4 (VBUS), P1.A9 (VBUS), P1.B4 (VBUS), P1.B9 (VBUS), U1.3 (VCCIO), U1.12 (VCC)
/external_io/+5V_usb: J50.1 (VBUS), J51.4
/external_io/RXD_uart: J43.2, U1.4 (RXD)
/external_io/TXD_uart: J43.3, U1.1 (TXD)
/external_io/full_color_led: D3.4 (DIN), J48.3
/external_io/sw_reset: J45.3, SW2.2
/external_io/usb_m: J50.2 (D-), J51.3
/external_io/usb_p: J50.3 (D+), J51.2
/md_fork/IN_A: J40.2, R10.1
/md_fork/IN_B: J40.3, R16.1
/md_fork/limit_sw_under: J16.2, J40.5, R24.2
/md_fork/limit_sw_upper: J14.2, J40.4, R22.2
GND: C1.2, C2.2, C5.2, C7.2, C9.2, C10.2, D4.1 (K), D5.1 (K), J21.1, J26.1, J55.1, J55.4, J55.7, J55.10, R26.2, U3.3 (GND), U7.1 (GND), U17.1 (GND)
GND1: D3.3 (VSS), J2.1, J3.1, J4.1, J5.1, J7.1, J14.1, J16.1, J23.1, J24.1, J25.1, J36.1, J37.1, J38.1, J40.1, J42.1, J43.1, J45.1, J48.1, J50.4 (GND), J50.5 (Shield), J51.1, J53.3, J60.4, J60.18, P1.A1 (GND), P1.A12 (GND), P1.B1 (GND), P1.B12 (GND), P1.S1 (SHIELD), R1.1, R2.1, R3.1, SW2.1, U1.5 (GND), U1.13 (GND), U5.2, U9.2, U11.2, U12.2, U13.2, U14.2 (GND), U14.7 (GND), U15.2, U16.2
unnamed: D4.2 (A), R27.2
unnamed: D5.2 (A), R28.1
unnamed: J2.2, J3.2, J4.2, J5.2, J7.2
unnamed: J12.1, U3.7 (OUT_A2), U3.8 (OUT_A1)
unnamed: J12.2, U3.5 (OUT_B2), U3.6 (OUT_B1)
unnamed: J17.1, J60.10
unnamed: J17.2, J60.8
unnamed: J17.3, J60.6
unnamed: J31.2, J32.2, J60.14, R38.2, U14.4 (SCL)
unnamed: J31.3, J32.3, J60.12, R37.2, U14.3 (SDA)
unnamed: J55.3, U16.3
unnamed: J55.6, U15.3
unnamed: J55.9, U12.3
unnamed: J55.12, U13.3
unnamed: P1.A5 (CC1), R3.2
unnamed: P1.B5 (CC2), R2.2
unnamed: Q3.2 (G), R26.1, U11.3
unnamed: R10.2, R14.1, U5.1
unnamed: R12.1, U5.4
unnamed: R16.2, R17.1, U9.1
unnamed: R18.1, U9.4
unnamed: R29.2, R30.1, U11.1
unnamed: R31.1, U11.4
unnamed: R32.2, R33.1, U12.1
unnamed: R36.1, U12.4
unnamed: R39.2, R40.1, U13.1
unnamed: R41.1, U13.4
unnamed: R42.2, R43.1, U15.1
unnamed: R44.1, U15.4
unnamed: R45.2, R46.1, U16.1
unnamed: R50.1, U16.4
unnamed: P1.A7 (D-), P1.B7 (D-), U1.9 (USBDM)
unnamed: P1.A6 (D+), P1.B6 (D+), U1.8 (USBDP)
unnamed: U3.1 (IN_A), U5.3
unnamed: U3.2 (IN_B), U9.3
Vin_3V3_cpu_hat: J23.6, J24.6, J25.6, J31.1, J32.1, J53.2, J60.2, R37.1, R38.1, U14.1 (VDD)
Vin_arm: J38.6, R30.2, R33.2, R40.2, R43.2, R46.2
Vin_cpu_hat: J42.4, J53.1, J60.16
Vin_md: J40.6, R14.2, R17.2, R22.1, R24.1

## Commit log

2025-02-04 persuade power board
2025-02-04 change .gitignore
2025-02-05 making usp
2025-02-06 made usp (sketch only)
2025-02-11 made all sketch for test (cpu board is only for test
2025-02-11 start attaching footprints. add some libraries
2025-02-11 attach all capacitors
2025-02-12 attach all the footprints
2025-02-19 change sketch a little
2025-02-19 plate power
2025-02-20 plate power and usp
2025-02-20 plate all parts
2025-02-21 wire and fill power board
2025-02-21 wiring and filling power complete
2025-02-21 complete wireing and filling usp
2025-02-21 wired and filled all borad
2025-02-21 solv errors waiting check
2025-02-21 change extern lib path to project dir
2025-02-22 add silk screen
2025-02-22 solv errors
2025-02-25 placed an order
2025-03-02 forgot to save
2025-03-03 replot
2025-03-04 order confirmed
2025-03-14 add bom
2025-03-16 add some info
2025-03-26 change name CORE->power_board moved cput power_borad to CORE
2025-03-26 fixed most of the error. waiting check
2025-03-31 complete power_board
2025-04-01 start making ORCA_CORE
2025-04-02 ordered power board
2025-04-03 add power registers to power_board gate driver
2025-04-06 almost completed CORE
2025-04-11 complete attaching footprint of CORE
2025-04-11 change .gitignore of CORE
2025-04-12 made board outline and import it
2025-04-14 place most of footprints. test replicate
2025-04-16 most of wire placed. try update kicad to use replicate library
2025-04-16 complete almost all wires. add mouse coms sensor
2025-04-18 end wiring
2025-04-19 correct fatal errors
2025-04-19 connect GND along every boards
2025-04-21 complete all CORE board. knew that 2 boards cannot be wrote in 1 sketch
2025-04-21 create outlines and pcb sketch files for A and B
2025-04-24 correct few errors in usp
2025-05-06 order comfirmed
2025-05-14 few tiny changes
2025-05-14 local_change in ubuntu
2025-05-14 add pdf
